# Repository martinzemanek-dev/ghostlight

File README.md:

# Ghostlight
Small board under a see-through miniature, to light it up. The board is powered by a battery and the light is programmable.
## Power supply
Circuit is expected to be build for 3V
### Battery
CR2032 for start. It needs holder at the bottom [BAT-HLD-001](https://cz.mouser.com/ProductDetail/712-BAT-HLD-001)
### Miscelenious
[MCP1700T-3302E/TT](https://cz.mouser.com/ProductDetail/Microchip-Technology/MCP1700T-3302E-TTVAO?qs=5aG0NVq1C4y9x%252BiC%252BXtIqg%3D%3D)
[1kF](https://cz.mouser.com/ProductDetail/TAIYO-YUDEN/MBASG168AB7105KTNA01?qs=sGAEpiMZZMukHu%252BjC5l7YRGYzw8qFBFXWJL8eB%2Fc1Uk%3D)
[100nF](https://cz.mouser.com/ProductDetail/TAIYO-YUDEN/MLASU105SB7104KFNB25?qs=sGAEpiMZZMukHu%252BjC5l7YRGYzw8qFBFXza8LoeCVgcc%3D)
[10uF](https://cz.mouser.com/ProductDetail/Murata-Electronics/GRM155C80G106ME18D?qs=doiCPypUmgHaqNm%2FsBDkxw%3D%3D)
[4.7 kilo ohm](https://www.gme.cz/v/1496357/yageo-r0603-4k7-01w-5-smd-rezistor)
## microcontroler
[STM32C011J4M6](https://cz.mouser.com/ProductDetail/511-STM32C011J4M6) (SO8 package) or [STM32C011J6M6](https://cz.mouser.com/cs/ProductDetail/511-STM32G030J6M6).

## LED
### LED control
[LP5817](https://cz.mouser.com/new/texas-instruments/ti-lp5817-3-channel-rgb-led-driver/) seems to be a good way to do it.
It will connect to u-controler to microcontroler. Communicates on I2C. Needs 100nF between Vcc and GND.
### LED component
While being small enough the [SB0606WC02-RGB](https://cz.mouser.com/ProductDetail/VCC/SB0606WC02-RGB?qs=rQFj71Wb1eX6WH%252BB20VtTw%3D%3D). Seems to be small and powered by 3V.

## Accelerometer
[LIS3DHTR](https://cz.mouser.com/ProductDetail/511-LIS3DHTR) seems to be a grat opinion. Its povered by up to 3.6V so the LDO should supply sufficient and safe power. It also communicates over I2C alongside LP5817 and doesn't collide in address. It will take over last free pins for interrupts. It also provides three analog outpusts, which can substitute the pins on the programming Ring for debuginng.

## Program
### Programing 
The board is programmeable with [STLINK-V3](https://cz.mouser.com/ProductDetail/511-STLINK-V3MINIE) with connected battery or powersupply. The programming pins are connected to ring of pins (Adapter between ring, programmer and power supply is currently work in progress). 

Here are pin functions going clockwise from pin 1.
| Pin | Function |
| --- | --- |
| 1 | Vdd (Power detection) |
| 2 | ST_LINK_SWCLK |
| 3 | ST_LINK_SWDIO |
| 4 | Unused |
| 5 | Unused |
| 6 | RESET |
| 7 | V_BATT |
| 8 | GND |

Programmer connected this way allows programming using STM32CubeProgrammer.
V_BATT is a dirrect connection to + of the battery.
It is also possible to connect external 3.3V power supply here, but only, when battery is disconnected.

### Logic

Current program rotates thrue multiple modes.
Upon Startup the device shortly blinks red and than is switchis to first program, which is shifts over few colours as a lavalamp.

After start-up, the program also starts checking on accelerometer status. 
Program goes thrue two fases, so the color would not change on accident.
First the program checks, if the device is tilted 90 degrees using X and Y acceleration from the accelerometer.
Than it waits, till the board is fully flipped and than it changes color.
All measurements are triggered by change interrupt from the LI3DH.
When Program color change is noticed, the program cycles true colors in following order.

| Order | Color |
| --- | --- |
| 1. | Lavalamp (slowly shifting colors) |
| 2. | Red |
| 3. | Green |
| 4. | Blue |
| 5. | Magenta |
| 6. | Yellow |
| 7. | Cyan |
| 8. | While |
| 9. | Off |
| 10. | Color visualization of the accelerometer output |

When the program displays static color it waits for an interrupt, before even checking the accelerometer.

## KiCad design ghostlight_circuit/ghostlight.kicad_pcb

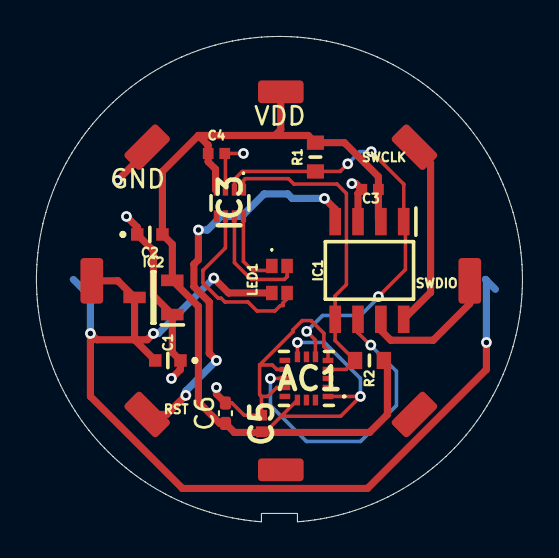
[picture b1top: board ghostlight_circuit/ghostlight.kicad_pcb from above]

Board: 2 copper layers, 27.0 x 27.0 mm, 15 parts (1 on the bottom side), 11 nets.

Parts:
AC1: LIS3DHTR
BT1: BAT-HLD-001; BATHLD001mod
C1, C2: MBASG168AB7105KTNA01; MBASx168
C3, C4, C5: MLASU105SB7104KFNB25; CAPC1005X55N
C6: GRM155C80G106ME18D; C_0402_1005Metric_Pad0.74x0.62mm_HandSolder
IC1: STM32C011J4M6; SOIC127P600X175-8N
IC2: MCP1700T-3302E_TT; SOT95P237X112-3N
IC3: LP5817DRLR
J1: Conn_01x08; Ring_connector_22mm
LED1: SB0606WC02-RGB; SB0606WC02RGB
R1, R2: SR0603JR-074R7L; RESC1608X55N

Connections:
3.3V: AC1.1 (VDDIO), AC1.8 (CS), AC1.14 (VDD), C2.2, C3.1, C4.2, C5.1, C6.1, IC1.2 (VDD/VDDA), IC2.2 (VOUT), IC3.4 (VCC), J1.1, R1.1, R2.1
ACC_INT1: AC1.11 (INT1), IC1.6 (PA12[PA10])
GND: AC1.5 (GND_1), AC1.10 (RES), AC1.12 (GND_2), BT1.3 (-), C1.1, C2.1, C3.2, C4.1, C5.2, C6.2, IC1.3 (VSS/VSSA), IC2.1 (GND), IC3.3 (GND), J1.8
unnamed: IC3.8 (OUT0), LED1.1 (K_R)
unnamed: IC3.7 (OUT1), LED1.2 (K_G)
unnamed: IC3.6 (OUT2), LED1.3 (K_B)
SCK: AC1.4 (SCL/SPC), IC1.5 (PA11[PA9]/PA8), IC3.1 (SCL), R2.2
SDA: AC1.6 (SDA/SDI/SDO), IC1.1 (PB7/PC14-OSCX_IN), IC3.2 (SDA), R1.2
ST_LIKN_SWCLK: IC1.8 (PB6/PA14-BOOT0/PC15-OSCX_OUT), J1.2
ST_LINK_SWDIO: IC1.7 (PA13), J1.3
V_BAT: BT1.1 (+_1), BT1.2 (+_2), C1.2, IC2.3 (VIN), J1.7, LED1.4 (COM_A)

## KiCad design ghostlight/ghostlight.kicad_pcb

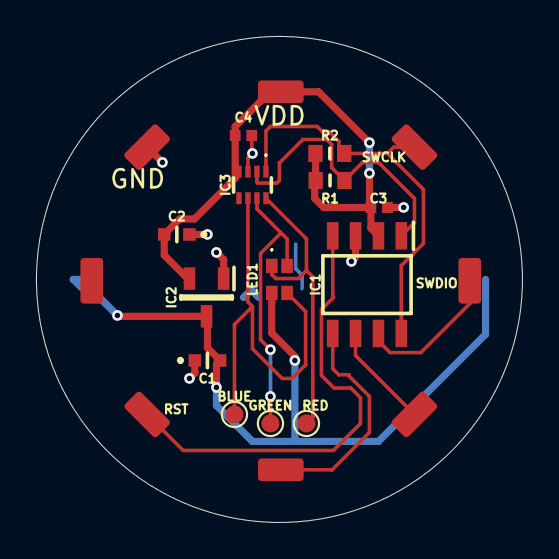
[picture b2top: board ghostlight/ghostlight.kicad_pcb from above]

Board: 2 copper layers, 27.0 x 27.0 mm, 15 parts (1 on the bottom side), 12 nets.

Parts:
BLUE: TP_B; TestPoint_Pad_D1.0mm
BT1: 3000; Battery_Holder_Lynx_CR2032
C1, C2: MBASG168AB7105KTNA01; MBASx168
C3, C4: MLASU105SB7104KFNB25; CAPC1005X55N
GREEN: TP_G; TestPoint_Pad_D1.0mm
IC1: STM32C011J4M6; SOIC127P600X175-8N
IC2: MCP1700T-3302E_TT; SOT95P237X112-3N
IC3: LP5817DRLR
J1: Conn_01x08; Ring_connector_22mm
LED1: SB0606WC02-RGB; SB0606WC02RGB
R1, R2: SR0603JR-074R7L; RESC1608X55N
RED: TP_R; TestPoint_Pad_D1.0mm

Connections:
3.3V: C2.2, C3.1, C4.2, IC1.2 (VDD/VDDA), IC2.2 (VOUT), IC3.4 (VCC), J1.1, R1.1, R2.1
GND: BT1.1 (+_1), C1.1, C2.1, C3.2, C4.1, IC1.3 (VSS/VSSA), IC2.1 (GND), IC3.3 (GND), J1.8
I2C_ERR: IC1.6 (PA12[PA10]), J1.4
LIVE: IC1.5 (PA11[PA9]/PA8), J1.5
unnamed: IC3.8 (OUT0), LED1.1 (K_R), RED.1 (1_1)
unnamed: GREEN.1 (1_1), IC3.7 (OUT1), LED1.2 (K_G)
unnamed: BLUE.1 (1_1), IC3.6 (OUT2), LED1.3 (K_B)
SCK: IC1.8 (PB6/PA14-BOOT0/PC15-OSCX_OUT), IC3.1 (SCL), J1.2, R2.2
SDA: IC1.1 (PB7/PC14-OSCX_IN), IC3.2 (SDA), R1.2
ST_LINK_RST/RST: IC1.4 (PA0/PA1/PA2/PF2-NRST), J1.6
ST_LINK_SWDIO: IC1.7 (PA13), J1.3
V_BAT: BT1.2 (+_2), BT1.3 (-), C1.2, IC2.3 (VIN), LED1.4 (COM_A)

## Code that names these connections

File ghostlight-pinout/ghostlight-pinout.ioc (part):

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Mcu.Name=STM32C011J(4-6)Mx
Mcu.Package=SO8N
Mcu.UserName=STM32C011J4Mx
PA12\ [PA10].GPIOParameters=GPIO_Label
PA12\ [PA10].GPIO_Label=I2C_ERROR
PA12\ [PA10].Signal=GPIO_Output
PA13.GPIOParameters=GPIO_Label
PA13.GPIO_Label=FLAG
PA13.Signal=GPIO_Output
PA8.GPIOParameters=GPIO_Label
PA8.GPIO_Label=LIVE
PA8.Signal=GPIO_Output
PA8__PA11\ [PA9].StandardMode=true
PB6.Mode=I2C
PB6.Signal=I2C1_SCL
PC14-OSCX_IN\ (PC14).Mode=I2C
PC14-OSCX_IN\ (PC14).Signal=I2C1_SDA
PC14-OSCX_IN\ (PC14)__PB7.StandardMode=true
PC15-OSCX_OUT\ (PC15)__PA14-BOOT0__PB6.StandardMode=true
PF2-NRST__PA0__PA1__PA2.StandardMode=true
RCC.HSE_VALUE=8000000
RCC.SYSCLKFreq_VALUE=12000000
board=custom

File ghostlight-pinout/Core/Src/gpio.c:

/* USER CODE BEGIN Header */
/**
  ******************************************************************************
  * @file    gpio.c
  * @brief   This file provides code for the configuration
  *          of all used GPIO pins.
  ******************************************************************************
  * @attention
  *
  * Copyright (c) 2026 STMicroelectronics.
  * All rights reserved.
  *
  * This software is licensed under terms that can be found in the LICENSE file
  * in the root directory of this software component.
  * If no LICENSE file comes with this software, it is provided AS-IS.
  *
  ******************************************************************************
  */
/* USER CODE END Header */

/* Includes ------------------------------------------------------------------*/
#include "gpio.h"

/* USER CODE BEGIN 0 */

/* USER CODE END 0 */

/*----------------------------------------------------------------------------*/
/* Configure GPIO                                                             */
/*----------------------------------------------------------------------------*/
/* USER CODE BEGIN 1 */

/* USER CODE END 1 */

/** Configure pins
*/
void MX_GPIO_Init(void)
{

  GPIO_InitTypeDef GPIO_InitStruct = {0};

  /* GPIO Ports Clock Enable */
  __HAL_RCC_GPIOC_CLK_ENABLE();
  __HAL_RCC_GPIOB_CLK_ENABLE();
  __HAL_RCC_GPIOF_CLK_ENABLE();
  __HAL_RCC_GPIOA_CLK_ENABLE();

  /*Configure GPIO pin Output Level */
  HAL_GPIO_WritePin(GPIOA, LIVE_Pin|I2C_ERROR_Pin|FLAG_Pin, GPIO_PIN_RESET);

  /*Configure GPIO pin : PB7 */
  GPIO_InitStruct.Pin = GPIO_PIN_7;
  GPIO_InitStruct.Mode = GPIO_MODE_ANALOG;
  GPIO_InitStruct.Pull = GPIO_NOPULL;
  HAL_GPIO_Init(GPIOB, &GPIO_InitStruct);

  /*Configure GPIO pin : PF2 */
  GPIO_InitStruct.Pin = GPIO_PIN_2;
  GPIO_InitStruct.Mode = GPIO_MODE_ANALOG;
  GPIO_InitStruct.Pull = GPIO_NOPULL;
  HAL_GPIO_Init(GPIOF, &GPIO_InitStruct);

  /*Configure GPIO pins : PA0 PA1 PA2 PA11
                           PA14 */
  GPIO_InitStruct.Pin = GPIO_PIN_0|GPIO_PIN_1|GPIO_PIN_2|GPIO_PIN_11
                          |GPIO_PIN_14;
  GPIO_InitStruct.Mode = GPIO_MODE_ANALOG;
  GPIO_InitStruct.Pull = GPIO_NOPULL;
  HAL_GPIO_Init(GPIOA, &GPIO_InitStruct);

  /*Configure GPIO pins : LIVE_Pin I2C_ERROR_Pin FLAG_Pin */
  GPIO_InitStruct.Pin = LIVE_Pin|I2C_ERROR_Pin|FLAG_Pin;
  GPIO_InitStruct.Mode = GPIO_MODE_OUTPUT_PP;
  GPIO_InitStruct.Pull = GPIO_NOPULL;
  GPIO_InitStruct.Speed = GPIO_SPEED_FREQ_LOW;
  HAL_GPIO_Init(GPIOA, &GPIO_InitStruct);

  /*Configure GPIO pin : PC15 */
  GPIO_InitStruct.Pin = GPIO_PIN_15;
  GPIO_InitStruct.Mode = GPIO_MODE_ANALOG;
  GPIO_InitStruct.Pull = GPIO_NOPULL;
  HAL_GPIO_Init(GPIOC, &GPIO_InitStruct);

  /**/
  HAL_SYSCFG_SetPinBinding(HAL_BIND_SO8_PIN1_PB7|HAL_BIND_SO8_PIN4_PF2|HAL_BIND_SO8_PIN4_PA0|HAL_BIND_SO8_PIN4_PA1
                          |HAL_BIND_SO8_PIN4_PA2|HAL_BIND_SO8_PIN5_PA8|HAL_BIND_SO8_PIN5_PA11|HAL_BIND_SO8_PIN8_PC15
                          |HAL_BIND_SO8_PIN8_PA14);

}

/* USER CODE BEGIN 2 */

/* USER CODE END 2 */

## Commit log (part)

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2026-03-25 Create empty KiCad project
2026-04-04 Update README.md
    Added estimated components
    Update README.md
    Correction of the titles
    Update README.md
    Correction of a link
2026-04-04 Update README.md
    Choosen specific consendators
2026-04-04 added first scheme for the board
2026-04-07 Add 2 missing cheme pages
2026-04-07 Add component shapes, to cheme
2026-04-07 added first board draft
2026-04-07 added custom ring for programming
2026-04-07 PDFs in this folder are now ignored
2026-04-07 optimalized the PCB
2026-04-09 Create folder for outputs
2026-04-17 Added missing link
2026-04-18 created MX project
2026-04-18 Autogenerate empty project
2026-04-18 regenerate the project and implement LP5817 Logic
2026-04-19 Add signal ports and basic program logic in main
2026-04-19 Implement program for LED + cleanup
2026-04-21 Progam, which should light up the let white
2026-04-21 change in schematic
2026-04-22 Add Test Points
2026-05-05 Add new battery holder
2026-05-05 Demo, which lights up the LED
2026-05-05 Update Components
    Some components were wrong, or wronglz choosen
2026-05-05 Board revision 2 - better spacing, test points and connect pins to ring
2026-05-06 program, which goes over all colors
2026-05-06 Reserve flash sector for reset count + management object
2026-05-06 Working program with color change
2026-05-07 rename folders
2026-05-13 rerouted the board
2026-05-14 Update README.md
    Add description of LIS3DH
2026-05-14 Update README.md
    Add supporting components
2026-05-14 Update README.md
    Add 10uF
2026-05-14 Added accelerometer to the schematic
2026-05-15 update pcb
    rerout and connect accelerometer
    better re-route
2026-05-15 rebase scheme repair
2026-06-03 TMP: added output files
2026-06-03 Update README.md
    Update readme for program and programming specifics, for version 2.0
2026-06-03 Update README.md
    Correction
2026-06-08 Update README.md
    removed duplicite section
